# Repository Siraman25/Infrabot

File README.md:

# **Infrarot-Roboter**
## **Beschreibung**
Bei diesen Inrarot-Robotern handelt es sich um zwei auf Rädern fahrenden Robotern welche als "Shooter-Spiel" konzipiert sind. Sie werden über zwei ESP-32 gesteuert (ESP32-CAM & ESP32-S2). Bedient werden sie entweder mit einem PS3-Controller oder über eine Website via PC oder Smartphone. Die Steuerung über PS3-Controller wird durch eine Bluetooth-Verbindung zwischen Controller und ESP32-S2 realisiert.\
Sie können sich gegenseitig abschießen. Dies wird mit Infrarot-Empfänger und -Sender realisiert. Für ein akustisches Feedback für Fehler, Schuss und Treffer werden Buzzer verwendet.\
Die Räder werden mit zwei 360°-Servomotoren angetriebn. Diese besitzen drei Pins: GND, +5V, Steuersingal. Die beiden Pins GND und +5V werden direkt an den Spannungsregler angeschlossen, da ein Servomotor ca. 550mA Strom zieht. Der Pin für das Steuersignal wird an den ESP32-S2 angeschlossen.\
Über eine Webseite, die auf dem ESP-S2 läuft, kann man den Videostream des ESP-CAM sehen.

Der Ordner "ESP32-CAM Code" enthält das funktionierende Code, im "Debug Code" Ordner befinden sich unwichtige Programme und Sketches, die wir fürs Debugging und fürs Testen benutzt haben. Der Ordner "ESP32-S2 Code" enthält das getestete Code für den ESP32-S2, dieser sollte einwandfrei funktionieren. Leider konnten wir es nicht aufbauen. Im "Web-Interface"-Ordner befindet sich der Boilerplate für die Web-Interface und eine kleine Dokumentation, wie das ausschauen hätte sollen. Dazu gibt es noch den Doku-Ordner.

## **Beschreibung**
##### Servo

<code>Name</code>: Continous servo FS90R
<code>Preis</code>: € 21,81	(4 Stück)
<code>Link</code>: [Click-here](https://it.aliexpress.com/item/32984667875.html?gatewayAdapt=glo2ita&spm=a2g0o.productlist.0.0.757d6a76EX7cRW&algo_pvid=e50159a6-6599-4880-aa28-8534ffaa9490&algo_exp_id=e50159a6-6599-4880-aa28-8534ffaa9490-0&pdp_ext_f=%7B%22sku_id%22%3A%2266784030012%22%7D)
##### Batteriehalterung

<code>Name</code>: 
<code>Preis</code>: 
<code>Link</code>: [Click-here]()
##### Powermanagement

<code>Name</code>: 
<code>Preis</code>: 
<code>Link</code>: [Click-here]()
##### ESP32 Cam-Module

<code>Name</code>: 113990580
<code>Preis</code>: € 8,99000 (1 Stück)
<code>Link</code>: [Click-here](https://www.digikey.it/it/products/detail/seeed-technology-co-ltd/113990580/9697033)
##### Hilfsrad

<code>Name</code>:  Universalrad
<code>Preis</code>:  € 5,95
<code>Link</code>: [Click-here](https://it.aliexpress.com/item/4001072165757.html?gatewayAdapt=glo2ita&spm=a2g0o.detail.1000014.41.601489317OgLFP&gps-id=pcDetailBottomMoreOtherSeller&scm=1007.13338.183347.0&scm_id=1007.13338.183347.0&scm-url=1007.13338.183347.0&pvid=666dd3e0-f355-4ce7-bd33-32656806e43c&_t=gps-id:pcDetailBottomMoreOtherSeller,scm-url:1007.13338.183347.0,pvid:666dd3e0-f355-4ce7-bd33-32656806e43c,tpp_buckets:668%232846%238111%231996&&pdp_ext_f=%7B%22sceneId%22:%2223416%22,%22sku_id%22:%2210000014060064385%22%7D)
##### Infrarot LED

<code>Name</code>: # TSAL6100
<code>Preis</code>: € 0,47000 (1 Stück)
<code>Link</code>: [Click-here](https://www.digikey.it/it/products/detail/vishay-semiconductor-opto-division/TSAL6100/1681338)
##### Infrarot Reciever

<code>Name</code>: TSSP58038
<code>Preis</code>: € 1,42000 (1 Stück)
<code>Link</code>: [Click-here](https://www.digikey.it/it/products/detail/vishay-semiconductor-opto-division/TSSP58038/4695717)
##### Button

<code>Name</code>: 
<code>Preis</code>: 
<code>Link</code>: [Click-here]()
##### Switch

<code>Name</code>: 
<code>Preis</code>: 
<code>Link</code>: [Click-here]()
##### Kühler

<code>Name</code>:  PS3-Controller
<code>Preis</code>: 
<code>Link</code>: [Click-here]()
##### Spannungsregler

<code>Name</code>:  LT1529-5
<code>Preis</code>: 
<code>Link</code>: [Click-here]()

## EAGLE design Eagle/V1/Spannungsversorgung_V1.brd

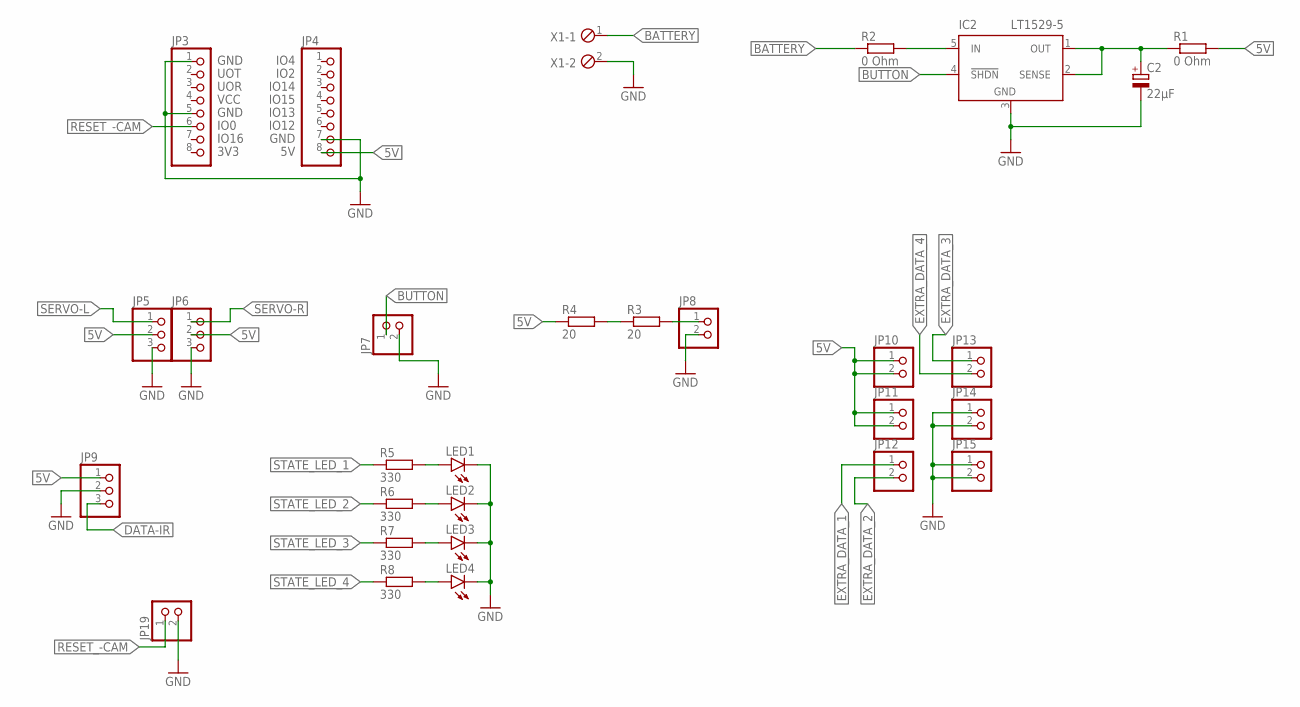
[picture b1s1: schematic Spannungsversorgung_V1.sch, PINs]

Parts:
C2: 22µF; E2,5-5
IC2: LT1529-5; TO220-5
JP3, JP4: PINHD-1X8; 1X08
JP5, JP6, JP9: PINHD-1X3; 1X03
JP7, JP8, JP10, JP11, JP12, JP13, JP14, JP15, JP19: PINHD-1X2; 1X02
LED1, LED2, LED3, LED4: LED3MM
R1, R2: 0 Ohm; R0805
R3, R4: 20; 0309/12
R5, R6, R7, R8: 330; R0805
X1: MPT2; 2POL254

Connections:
5V: JP4.8, JP5.2, JP6.2, JP9.1, JP10.1, JP10.2, JP11.1, JP11.2, R1.2, R4.1
BATTERY: R2.1, X1.1
BUTTON: IC2.4 (!SHDN), JP7.1
DATA-IR: JP9.3
EXTRA_DATA_1: JP12.1
EXTRA_DATA_2: JP12.2
EXTRA_DATA_3: JP13.1
EXTRA_DATA_4: JP13.2
GND: C2.-, IC2.3 (GND), JP3.1, JP3.5, JP4.7, JP5.3, JP6.3, JP7.2, JP8.2, JP9.2, JP14.1, JP14.2, JP15.1, JP15.2, JP19.2, LED1.K (C), LED2.K (C), LED3.K (C), LED4.K (C), X1.2
unnamed: R3.1, R4.2
unnamed: JP8.1, R3.2
unnamed: IC2.5 (IN), R2.2
unnamed: C2.+, IC2.1 (OUT), IC2.2 (SENSE), R1.1
unnamed: LED1.A, R5.2
unnamed: LED2.A, R6.2
unnamed: LED3.A, R7.2
unnamed: LED4.A, R8.2
RESET_-CAM: JP3.6, JP19.1
SERVO-L: JP5.1
SERVO-R: JP6.1
STATE_LED_1: R5.1
STATE_LED_2: R6.1
STATE_LED_3: R7.1
STATE_LED_4: R8.1

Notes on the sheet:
3V3
IO16
IO0
GND
VCC
UOR
UOT
IO12
IO13
IO15
IO14
IO2
IO4

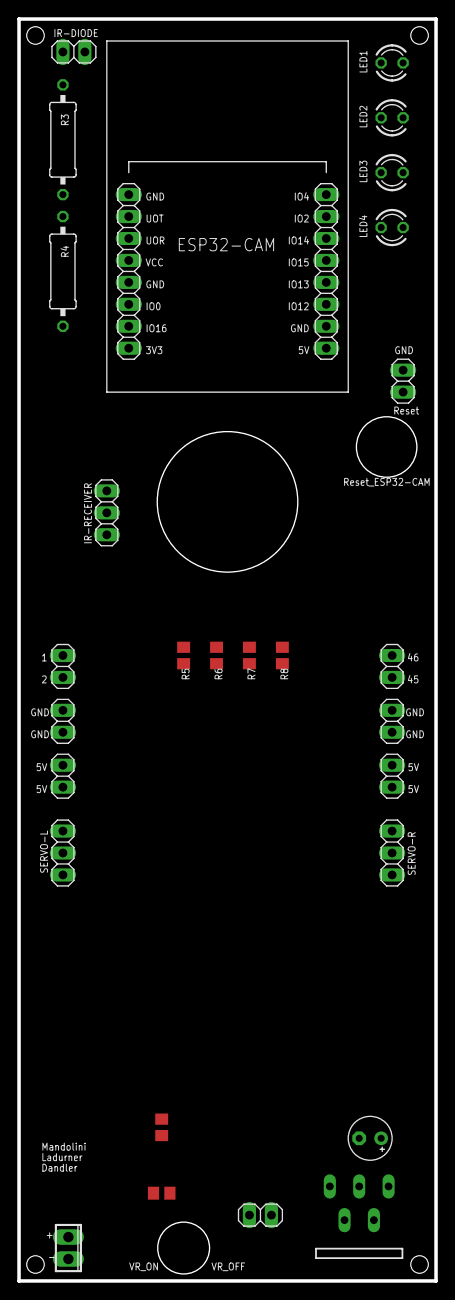
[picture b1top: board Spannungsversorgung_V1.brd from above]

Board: 2 copper layers, 48.3 x 146.1 mm, 29 parts (0 on the bottom side), 13 nets.

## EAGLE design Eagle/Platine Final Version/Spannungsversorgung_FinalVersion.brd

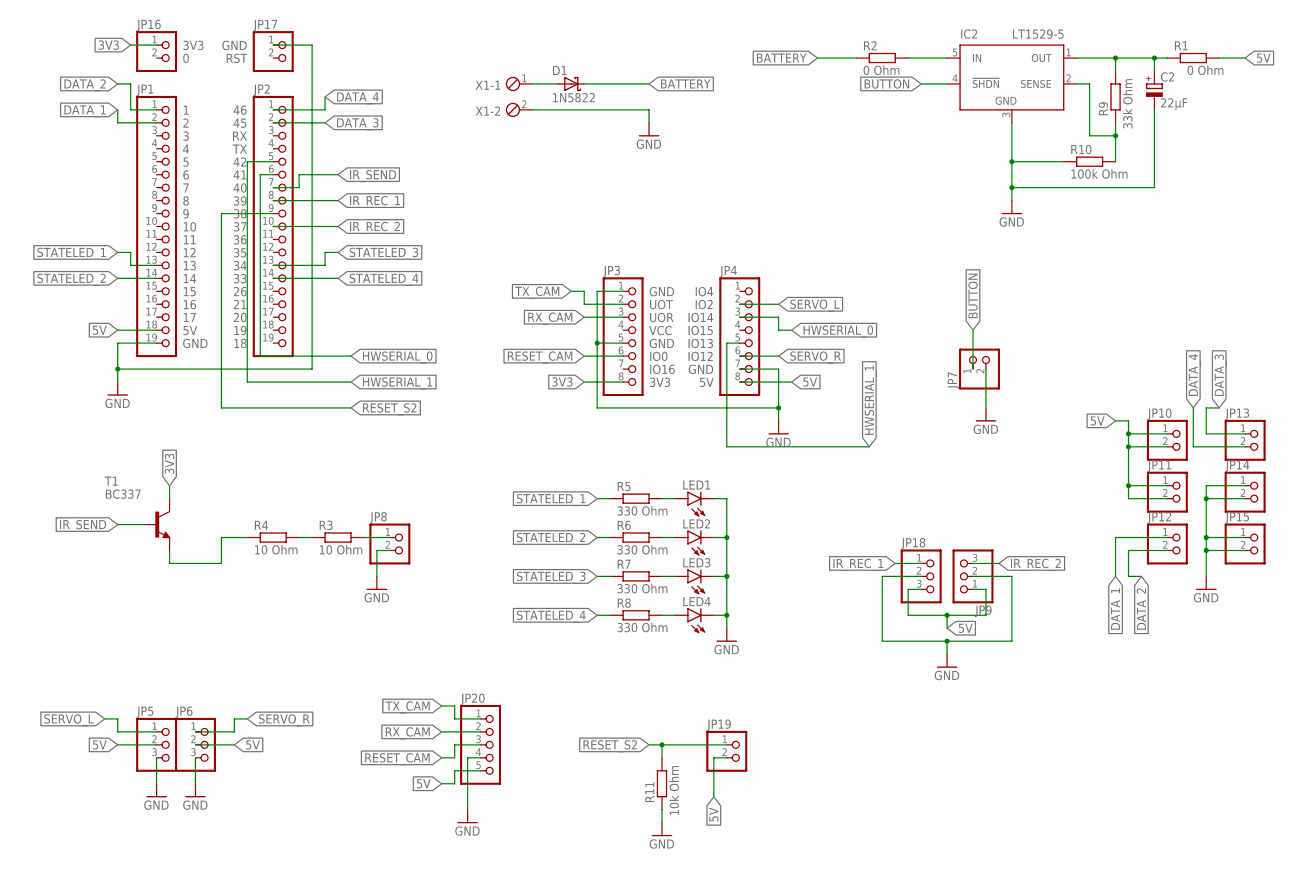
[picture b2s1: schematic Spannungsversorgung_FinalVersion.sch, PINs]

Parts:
C2: 22µF; E2,5-5
D1: 1N5822; DIOAD2120W130L950D530P
IC2: LT1529-5; TO220-5
JP1, JP2: PINHD-1X19; 1X19
JP3, JP4: PINHD-1X8; 1X08
JP5, JP6, JP9, JP18: PINHD-1X3; 1X03
JP7, JP8, JP10, JP11, JP12, JP13, JP14, JP15, JP16, JP17, JP19: PINHD-1X2; 1X02
JP20: PINHD-1X5; 1X05
LED1, LED2, LED3, LED4: LED3MM
R1, R2: 0 Ohm; R0805
R3, R4: 10 Ohm; 0309/12
R5, R6, R7, R8: 330 Ohm; R0805
R9: 33k Ohm; 0309/12
R10: 100k Ohm; 0309/12
R11: 10k Ohm; 0309/12
T1: BC337; TO92
X1: MPT2; 2POL254

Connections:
3V3: JP3.8, JP16.1, T1.3 (C)
5V: JP1.18, JP4.8, JP5.2, JP6.2, JP9.1, JP10.1, JP10.2, JP11.1, JP11.2, JP18.3, JP19.2, JP20.5, R1.2
BATTERY: D1.C, R2.1
BUTTON: IC2.4 (!SHDN), JP7.1
DATA_1: JP1.2, JP12.1
DATA_2: JP1.1, JP12.2
DATA_3: JP2.2, JP13.1
DATA_4: JP2.1, JP13.2
GND: C2.-, IC2.3 (GND), JP1.19, JP3.1, JP3.5, JP4.7, JP5.3, JP6.3, JP7.2, JP8.2, JP9.2, JP14.1, JP14.2, JP15.1, JP15.2, JP17.1, JP18.2, JP20.4, LED1.K (C), LED2.K (C), LED3.K (C), LED4.K (C), R10.1, R11.1, X1.2
HWSERIAL_0: JP2.6, JP4.3
HWSERIAL_1: JP2.5, JP4.5
IR_REC_1: JP2.8, JP18.1
IR_REC_2: JP2.10, JP9.3
IR_SEND: JP2.7, T1.2 (B)
unnamed: R3.1, R4.2
unnamed: JP8.1, R3.2
unnamed: IC2.5 (IN), R2.2
unnamed: D1.A, X1.1
unnamed: LED1.A, R5.2
unnamed: LED2.A, R6.2
unnamed: LED3.A, R7.2
unnamed: LED4.A, R8.2
unnamed: R4.1, T1.1 (E)
unnamed: IC2.2 (SENSE), R9.1, R10.2
unnamed: C2.+, IC2.1 (OUT), R1.1, R9.2
RESET_CAM: JP3.6, JP20.3
RESET_S2: JP2.9, JP19.1, R11.2
RX_CAM: JP3.3, JP20.2
SERVO_L: JP4.2, JP5.1
SERVO_R: JP4.6, JP6.1
STATELED_1: JP1.13, R5.1
STATELED_2: JP1.14, R6.1
STATELED_3: JP2.13, R7.1
STATELED_4: JP2.14, R8.1
TX_CAM: JP3.2, JP20.1

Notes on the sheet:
3V3
IO16
GND
IO0
IO12
IO13
UOR
IO14
VCC
IO15
UOT
IO2
IO4
RST

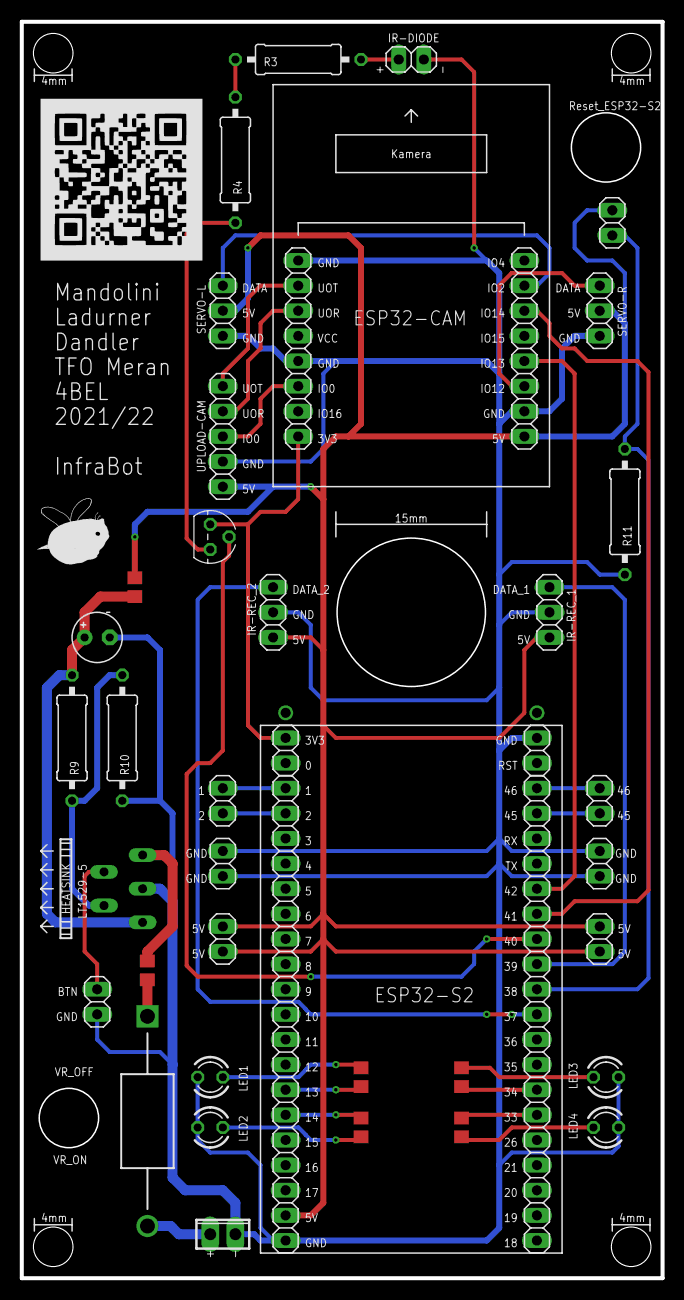
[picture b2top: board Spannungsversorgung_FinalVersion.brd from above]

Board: 2 copper layers, 64.8 x 127.0 mm, 40 parts (0 on the bottom side), 35 nets.

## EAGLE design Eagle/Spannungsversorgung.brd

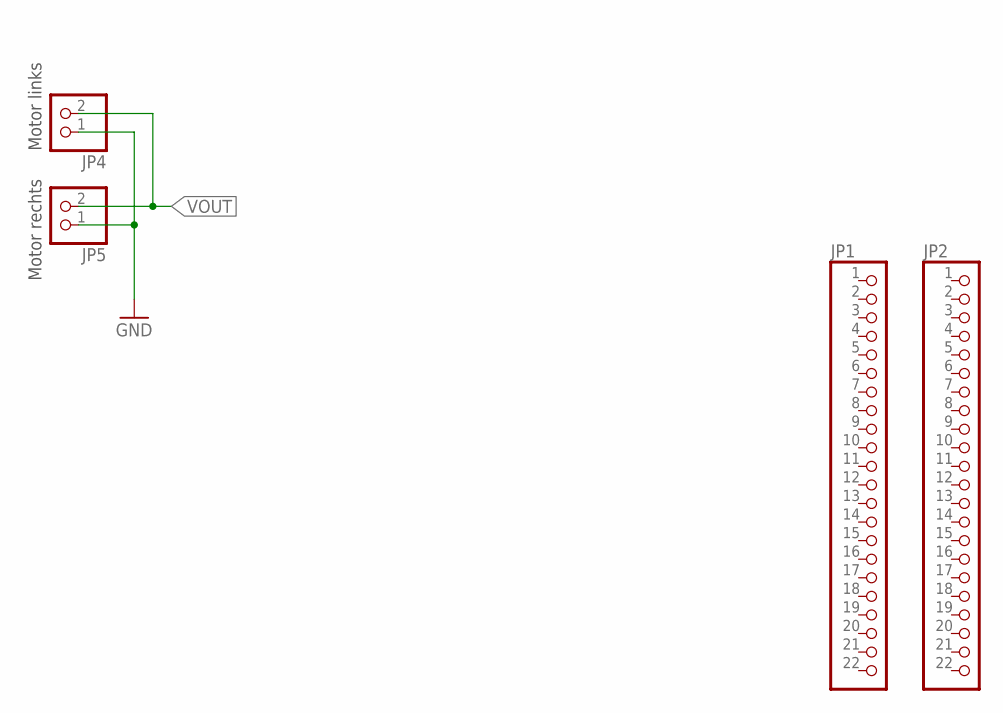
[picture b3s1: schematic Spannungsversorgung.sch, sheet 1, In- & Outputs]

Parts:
JP1, JP2: PINHD-1X22; 1X22
JP4, JP5: PINHD-1X2; 1X02

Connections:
GND: JP4.1, JP5.1; also elsewhere on the board
VOUT: JP4.2, JP5.2; also elsewhere on the board

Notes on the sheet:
Motor links
Motor rechts

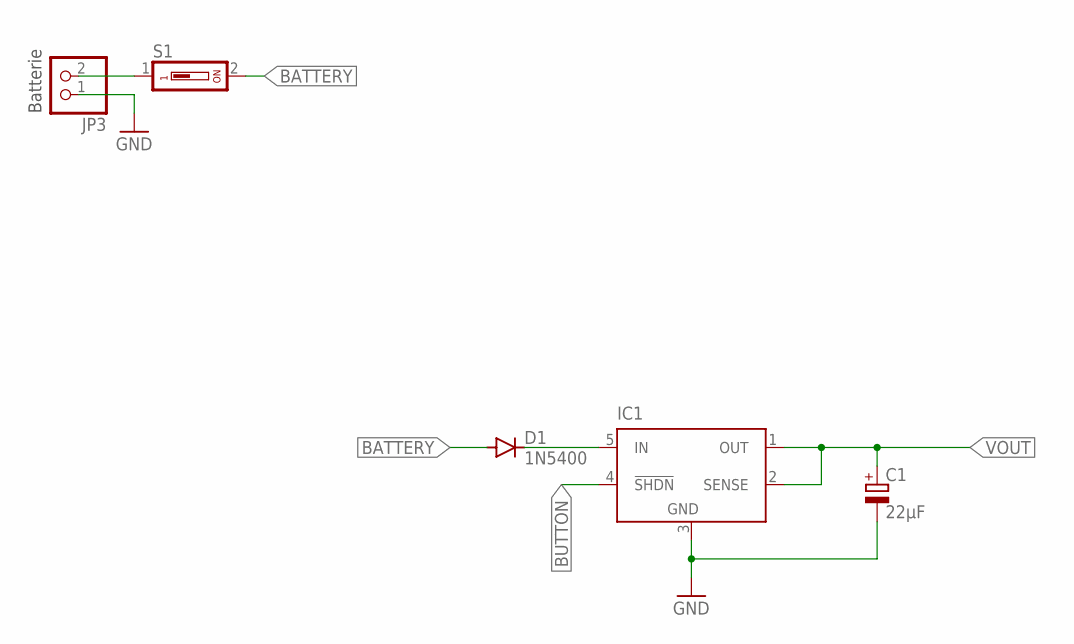
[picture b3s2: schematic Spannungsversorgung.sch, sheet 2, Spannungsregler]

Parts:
C1: 22µF; E2,5-5
D1: 1N5400; DO201-15
IC1: LT1529T; TO220-5
JP3: PINHD-1X2; 1X02
S1: DS01; DS-01

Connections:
BATTERY: D1.A, JP3.2, S1.1, S1.2
BUTTON: IC1.4 (!SHDN)
GND: C1.-, IC1.3 (GND), JP3.1; also elsewhere on the board
unnamed: D1.C, IC1.5 (IN)
VOUT: C1.+, IC1.1 (OUT), IC1.2 (SENSE); also elsewhere on the board

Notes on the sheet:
Batterie

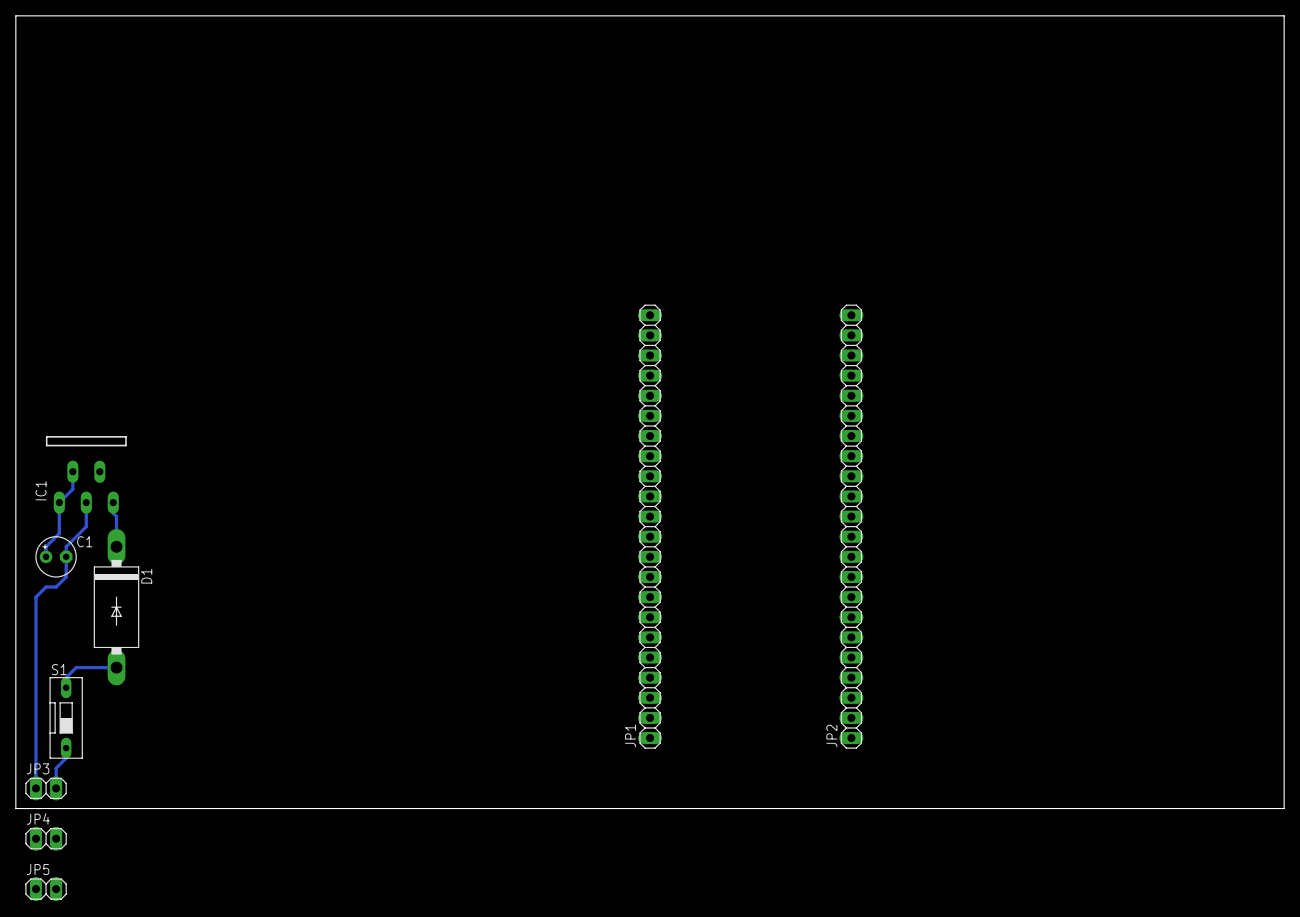
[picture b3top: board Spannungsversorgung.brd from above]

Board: 2 copper layers, 160.0 x 100.0 mm, 9 parts (0 on the bottom side), 4 nets.

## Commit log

2021-10-06 Included the Eagel Schematic and Board
2021-10-15 Added 'IR-robo-motor' test program
2021-11-10 Connecting Ps3 Controller
2021-11-10 Added PinHeads to the Eagle file
2021-11-10 Added a leagend for the controls of the robo
2021-11-24 Changed the structur of the ps3 programm
2021-11-24 Added initial web-interface boilerplate and docs-folder
2021-11-24 Created Spannungsregler.md
2021-12-01 Added Features & Verwendung to the documentation of LT1529-5
2021-12-01 Included images in the docu
2021-12-01 Created folder "Bilder" for images
2021-12-01 continuing of PS3 controller
2021-12-02 Added image "Spannungsregler_DropoutVoltage"
2021-12-02 Added image "Spannungsregler_Kühler"
2021-12-02 Added "Thermische Problme" & "Pins" as subtopics at the docu "Spannungsregler"
2021-12-02 Edited the layout at the documentation "Spannungsregler"
2021-12-06 Added image "Spannungsregler_ThermischerWiderstand"
2021-12-06 Changed image "Spannungsregler_ThermischerWiderstand"
2021-12-06 Added "Leistungsberechnung" as subtopics at the documentation "Spannungsregler"
2021-12-06 Changed the layout at the documentation "Spannungsregler"
2021-12-15 Changed the equal sing
2021-12-15 Added all Fusion360 and Blender sketches
2021-12-15 Deletet all Fusion360 and Blender sketches
2021-12-22 beginn of the Servo
2022-01-03 Dokumentationn
2022-01-14 change of code for servo
2022-01-15 Servos are Working now. Added new File for a new Version of The ps3_Code
2022-01-19 Created the ps3Controller.md
2022-01-19 Modified Ps3Controller.md
2022-01-26 Documentary of Ps3_Controller & Servo
2022-01-26 Documentation Ps3_Controller
2022-01-26 Dokumentation Ps3_Controller
2022-01-26 Started work on infrared and WiFi data exchange between ESPs.
2022-01-26 Add image "Connection_PS3_ESP32"
2022-01-26 Started the edit of the "Readme.md"
2022-01-26 Added two images to the "Readme.md"
2022-01-26 Managed simplex communication over WiFi (master -> slave)
2022-01-26 Uploaded a newer version of Spannungsregler_Kühler.png
2022-01-26 Updated the Spannungsregler.md
2022-01-26 Added the newer version of Spannungsregler_Kühler.png to the Spannungsregler.md
2022-02-10 Improved data exchange over WiFi between the two ESP32-CAMs
2022-02-17 The problem that came with switching from esp32 to esp32S2
2022-03-06 Changed some things, added global .gitignore
2022-03-06 Added trial-code and "final code" in Final Code folder, eventual code deemed to be final needs to be added there
2022-03-07 Added pin description for PCB-design
2022-03-09 Updated Pins
2022-03-20 Updated the images from the folder "Spannungsregler"
2022-03-20 Added "Berechnung Spannungsteiler" to the docu
2022-03-20 Added the final version for the PCB to the repo
2022-03-20 Edited the layout for the docu "Spannungsregler"
2022-03-30 Added "Maße für FÜLA.md"
2022-03-30 Updated the Reamde.md
2022-03-30 deleted hardware.md
2022-03-30 Add a schematic for the communication between the devices
2022-03-30 Add the docu "Datenaustausch.md"
2022-03-30 Changing name for Pictures
2022-03-30 added Images into the Readme.md
2022-04-13 Dokumentation
2022-05-11 Added protokoll
2022-05-17 Added a video as a documentation for the driving process
2022-05-17 Doku, Salvage and Final code
2022-05-31 Refactoring of repo structure
